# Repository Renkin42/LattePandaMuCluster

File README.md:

Latte Panda Mu Cluster Board
============================

This is a Mini-DTX cluster board for five Latte Panda Mu system-on-modules. Each slot recieves two sata connections, an m.2 M-key slot at pcie gen3x2 and a 2.5gb ethernet 
connection via an RTL8125B. Slot 1 has two USB-3 connections broken out to the rear IO along with HDMI and a single USB Type C port on a front panel header. Slots 2 and 3 
Each have a Front USB-3 connection, a rear USB-3 connection, and an M.2 E-key slot. Slots 4 and 5 have an open-back pcie gen 3x4 slot.

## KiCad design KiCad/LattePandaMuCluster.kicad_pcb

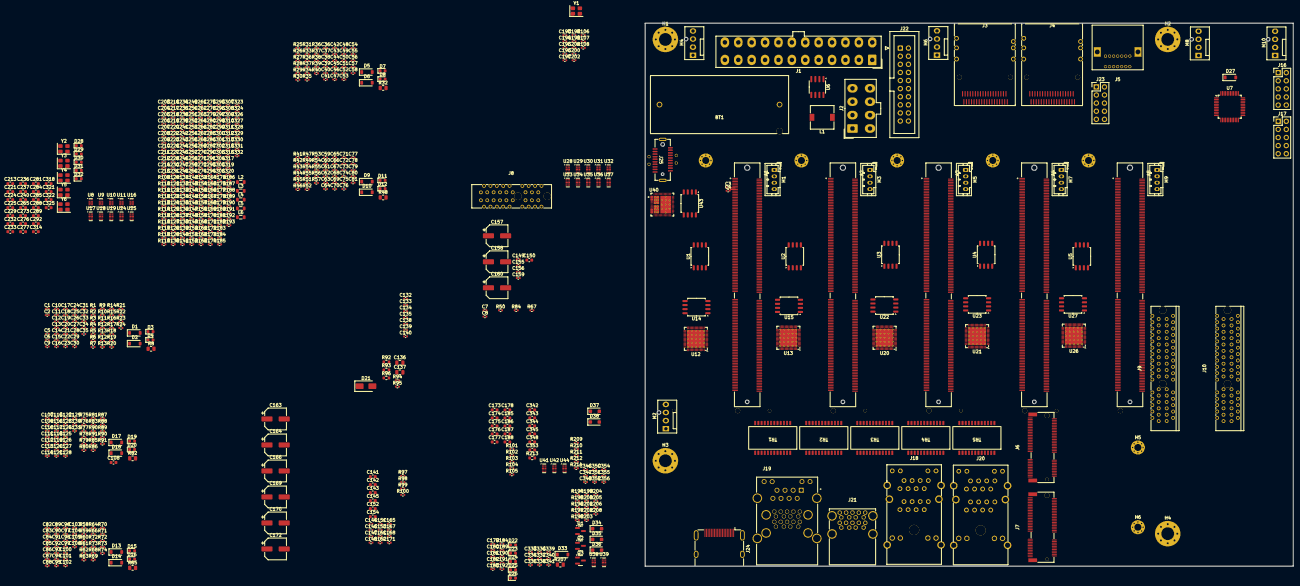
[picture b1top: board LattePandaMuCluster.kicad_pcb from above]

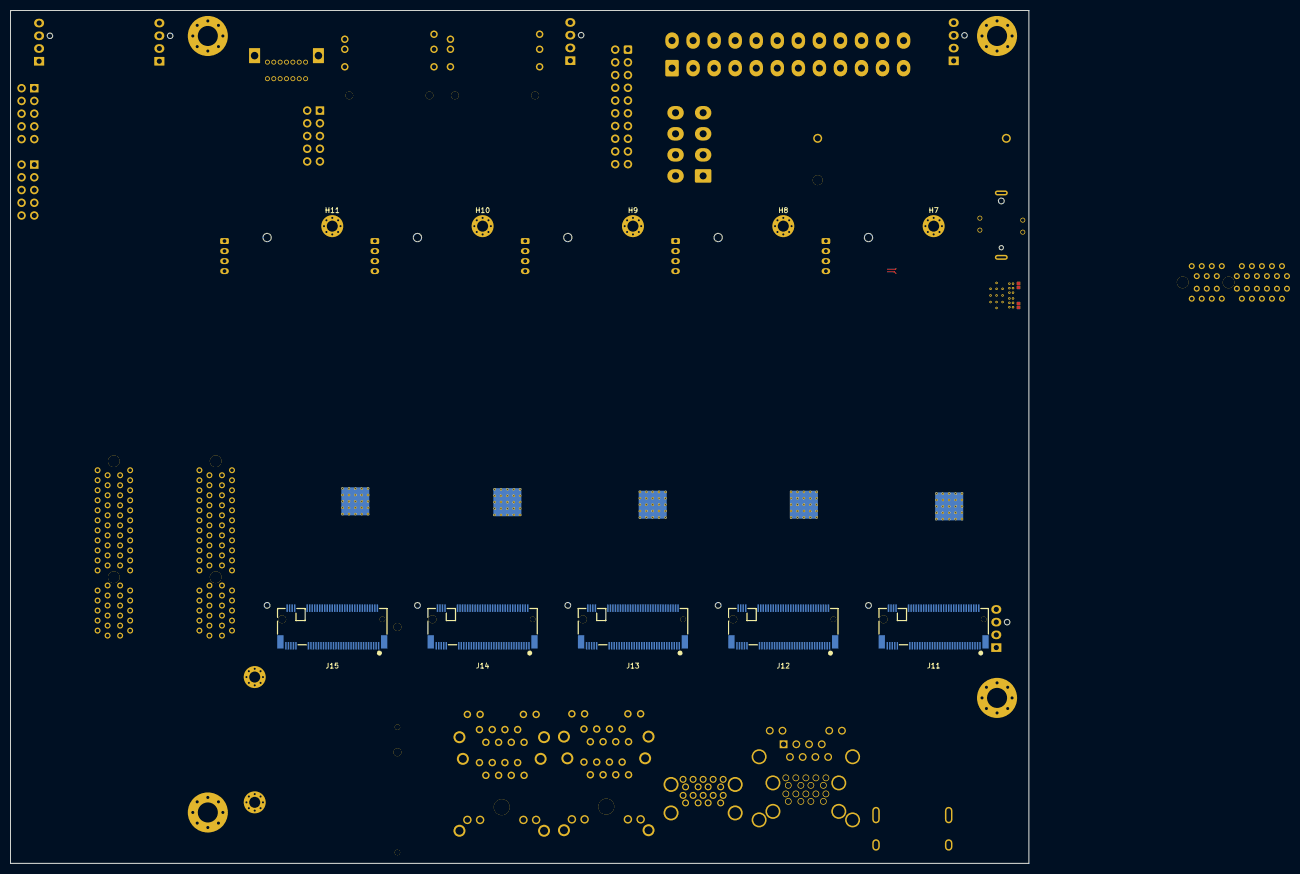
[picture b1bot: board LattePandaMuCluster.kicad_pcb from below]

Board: 4 copper layers, 203.2 x 170.2 mm, 734 parts (10 on the bottom side), 807 nets.

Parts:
A1, A2, A3, A4, A5: LattePanda_Mu; ATTEND_124B-150A02
BT1: Battery_Cell; BAT-TH_BH-123A-A5BJ002
C1, C2, C3, C4, C5, C6, C23, C26, C27, C36, C37, C38, C39, C40, C41, C58, C59, C60, C61, C62, C63, C64, C81, C82, C83, C106, C107, C131, C132, C144, C146, C147, C148, C179, C180, C181, C182, C183, C184, C189, C190, C191, C192, C194, C195, C197, C203, C204, C205, C206, C207, C208, C209, C210, C211, C212, C214, C215, C216, C217, C218, C219, C220, C222, C223, C226, C227, C228, C230, C231, C234, C235, C238, C239, C245, C247, C255, C256, C257, C258, C259, C260, C261, C262, C263, C264, C266, C267, C268, C269, C270, C271, C272, C274, C275, C278, C279, C280, C282, C283, C286, C287, C290, C291, C297, C299, C307, C308, C309, C310, C311, C312, C313, C315, C316, C317, C319, C320, C323, C324, C328, C333, C334, C335, C336, C337, C338, C339, C340, C341, C356: 100nF; C_0402_1005Metric
C7, C8, C9, C10, C11, C12, C21, C22, C30, C31, C34, C35, C42, C43, C44, C45, C46, C47, C56, C57, C65, C66, C67, C68, C69, C70, C79, C80, C84, C85, C86, C87, C88, C89, C90, C91, C92, C93, C94, C95, C104, C105, C109, C110, C111, C112, C113, C114, C115, C116, C117, C118, C119, C120, C129, C130, C241, C242, C243, C244, C293, C294, C295, C296, C326, C327: 220nF; C_0402_1005Metric
C13, C14, C15, C16, C17, C18, C19, C20, C48, C49, C50, C51, C52, C53, C54, C55, C71, C72, C73, C74, C75, C76, C77, C78, C96, C97, C98, C99, C100, C101, C102, C103, C121, C122, C123, C124, C125, C126, C127, C128, C133, C138, C198, C349, C350, C351, C352: 10nF; C_0402_1005Metric
C24, C25, C249, C250, C301, C302, C330: 100pF; C_0402_1005Metric
C28, C29, C32, C33: 330nF; C_0402_1005Metric
C108: 100nF; C_0603_1608Metric
C134, C135, C193: 4.7uF; C_0402_1005Metric
C136, C137: 47uF; C_0805_2012Metric
C139: 1nF; C_0402_1005Metric
C140: 47pF; C_0402_1005Metric
C141, C142, C143, C145, C173, C174, C175, C176, C177, C178, C185, C186, C187, C188, C342, C343, C344, C345, C348: 10uF; C_0603_1608Metric
C149, C151, C153, C155, C156, C159, C161, C162, C165, C167, C168, C171: 100nF/50V; C_0402_1005Metric
C150, C152, C154: 10uF/10V; C_0603_1608Metric
C157, C158, C163, C164, C169, C170: 100uF/25V; CP_Elec_6.3x7.7
C160, C166, C172: 560uF/25V; CP_Elec_6.3x7.7
C196, C199, C200, C346, C347: 1uF; C_0402_1005Metric
C201, C202, C251, C252, C253, C254, C303, C304, C305, C306, C331, C332: 27pF; C_0402_1005Metric
C213, C221, C224, C225, C229, C232, C233, C236, C237, C240, C265, C273, C276, C277, C281, C284, C285, C288, C289, C292, C314, C318, C321, C322, C325, C353: 22uF; C_0603_1608Metric
C246, C248, C298, C300, C329: 390pF; C_0402_1005Metric
C354, C355: 220pF; C_0402_1005Metric
D1, D2, D5, D6, D9, D10, D13, D14, D17, D18, D27, D33: B0520W; D_SOD-123
D3, D4, D7, D8, D11, D12, D15, D16, D19, D20, D22, D23, D24, D25, D26, D28, D29, D30, D31, D32: LED; LED_0603_1608Metric
D21: SSL345F; D_SMA
D34, D35, D36, D37, D38: SMF33A; D_SOD-123F
H1, H2, H3, H4: MountingHole_Pad; MountingHole_4mm_Pad_Via
H5, H6, H7, H8, H9, H10, H11: MountingHole_Pad; MountingHole_2.2mm_M2_Pad_Via
J1: ATX-24; Molex_Mini-Fit_Jr_5566-24A_2x12_P4.20mm_Vertical
J2: Conn_02x04_Top_Bottom; Molex_Mini-Fit_Jr_5566-08A_2x04_P4.20mm_Vertical
J3, J4: SFF-8087; CONN-SMD_LD2136V-MCUL6
J5: SATA; CONN-TH_XUTS-0722-2070
J6, J7: Bus_M.2_Socket_E; CONN-SMD_AS0BC21-S48BE-7H
J8: Bus_PCI_Express_x1; CONN-TH_HYCW05-PCI36-155B
J9, J10: Bus_PCI_Express_x4; PCIE-TH_AAA-PCI-161-K03
J11, J12, J13, J14, J15: Bus_M.2_Socket_M; CONN-SMD_AS0BC21-S30BM-7H
J16, J17, J23: Conn_02x05_Odd_Even; PinHeader_2x05_P2.54mm_Vertical
J18, J20: RJ45_LED_Shielded_x2; RJ45-TH_HC-RJ45-059C
J19: RJE361882415; AMPHENOL_RJE361882415
J21: USB3_A_Stacked; USB-A-TH_HC-USB3.0-L175-2X1-J
J22: USB3_IDC; IDC-Header_2x10_P2.54mm_Vertical
J24: HDMI_A; HDMI_A_Molex_208658-1001_Horizontal
J25: JACK-USBE-20PINTL
L1: 6.8uH; L_7.3x7.3_H3.5
L2, L3, L4, L5, L6: 1uH; L_0805_2012Metric
M1, M3, M5, M7, M9: Fan_4pin; JST_PH_B4B-PH-K_1x04_P2.00mm_Vertical
M2, M4, M6, M8, M10: Fan_4pin; FanPinHeader_1x04_P2.54mm_Vertical
Q1, Q2, Q3: 2N7002; SOT-23
R1, R2, R25, R26, R41, R42, R58, R59, R75, R76: 4.7k; R_0402_1005Metric
R3, R4, R7, R27, R28, R31, R43, R44, R47, R60, R61, R64, R77, R78, R81, R115, R117, R149, R151, R180, R208: 22k; R_0402_1005Metric
R5, R6, R10, R11, R13#2, R14, R15, R16, R17, R18, R29, R30, R45, R46, R62, R63, R79, R80: 100R; R_0402_1005Metric
R8, R32, R48, R65, R82, R207: 1k; R_0805_2012Metric
R9, R12, R33, R34, R49, R51, R66, R68, R83, R85, R101, R102, R103, R104, R105, R202, R203, R205, R206: 2.2k; R_0402_1005Metric
R12#2, R13, R19, R20, R22, R36, R36#2, R37, R37#2, R39, R50, R53, R54, R54#2, R55, R56, R67, R70, R71, R72, R73, R73#2, R84, R87, R88, R90, R90#2, R91, R97, R98, R99, R100, R108, R109, R110, R111, R112, R131, R132, R133, R134, R135, R136, R137, R138, R139, R140, R141, R142, R143, R144, R145, R146, R165, R166, R167, R168, R169, R170, R171, R172, R173, R174, R175, R176, R177, R178, R188, R189, R190, R191, R192, R193, R209, R210, R212, R214: 10k; R_0402_1005Metric
R21, R23, R24, R35, R38, R40, R52, R55#2, R57, R69, R72#2, R74, R86, R89, R91#2, R211: 100k; R_0402_1005Metric
R92: 82k; R_0603_1608Metric
R93: 27k; R_0603_1608Metric
R94: 75k; R_0402_1005Metric
R95: 24k; R_0402_1005Metric
R96: 30k; R_0603_1608Metric
R106, R107, R113, R114, R116, R118, R129, R130, R147, R148, R150, R152, R163, R164, R179, R181, R187: 510R; R_0402_1005Metric
R119, R120, R153, R154, R182: 200R; R_0402_1005Metric
R121, R122, R123, R124, R125, R126, R127, R128, R155, R156, R157, R158, R159, R160, R161, R162, R183, R184, R185, R186: 75R; R_0402_1005Metric
R194, R195, R196, R197, R198, R199, R200, R201: 470R; R_0402_1005Metric
R204: 1M; R_0402_1005Metric
R213: 62k; R_0603_1608Metric
TR1, TR2, TR3, TR4, TR5: QG2439S
U1, U2, U3, U4, U5, U14, U15, U22, U23, U27, U43: ZD25Q64BSIGT; SOIC-8_5.3x5.3mm_P1.27mm
U6: TPS54331; SOIC-8_3.9x4.9mm_P1.27mm
U7: STM32F030C8Tx; LQFP-48_7x7mm_P0.5mm
U8, U9, U10, U11, U16, U17, U18, U19, U24, U25, U28, U29, U30, U31, U32, U33, U34, U35, U36, U37, U38, U39, U41, U42, U44: H5VU25U; Diodes_UDFN-10_1.0x2.5mm_P0.5mm
U12, U13, U20, U21, U26: KTI226V; QFN-56-1EP_7x7mm_P0.4mm_EP5.6x5.6mm_ThermalVias
U40: TPS65987DDJRSHR; RSH0056E-MFG
Y1, Y2, Y3, Y4, Y5, Y6: 25MHz; Crystal_SMD_3225-4Pin_3.2x2.5mm

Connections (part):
+3V3: C23.1, C58.1, C81.1, C106.1, C131.1, C141.1, C142.1, C143.1, C144.1, C145.1, C146.1, C147.1, C148.1, C159.1, C160.1, C165.1, C166.1, C171.1, C172.1, C173.1, C174.1, C175.1, C176.1, C177.1, C178.1, C179.1, C180.1, C181.1, C182.1, C183.1, C184.1, C185.1, C186.1, C187.1, C188.1, C189.1, C190.1, C191.1, C192.1, J1.1 (+3.3V), J1.2 (+3.3V), J1.12 (+3.3V), J1.13 (+3.3V), J6.2 (3.3V), J6.4 (3.3V), J6.72 (3.3V), J6.74 (3.3V), J7.2 (3.3V), J7.4 (3.3V), J7.72 (3.3V), J7.74 (3.3V), J9.A9 (+3.3V), J9.A10 (+3.3V), J9.B8 (+3.3V), J10.A9 (+3.3V), J10.A10 (+3.3V), J10.B8 (+3.3V), J11.2 (3.3V), J11.4 (3.3V), J11.12 (3.3V), J11.14 (3.3V), J11.16 (3.3V), J11.18 (3.3V), J11.70 (3.3V), J11.72 (3.3V), J11.74 (3.3V), J12.2 (3.3V), J12.4 (3.3V), J12.12 (3.3V), J12.14 (3.3V), J12.16 (3.3V), J12.18 (3.3V), J12.70 (3.3V), J12.72 (3.3V), J12.74 (3.3V), J13.2 (3.3V), J13.4 (3.3V), J13.12 (3.3V), J13.14 (3.3V), J13.16 (3.3V)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
+3V3SB: C136.1, C137.1, C149.2, C150.2, C151.2, C152.2, C153.2, C154.2, C203.2, C204.2, C205.1, C206.2, C207.2, C208.1, C211.2, C212.1, C213.2, C214.1, C217.2, C218.1, C221.2, C222.1, C225.2, C226.1, C229.2, C230.1, C233.2, C234.1, C237.2, C238.1, C245.1, C247.1, C255.2, C256.2, C257.1, C258.2, C259.2, C260.1, C263.2, C264.1, C265.2, C266.1, C269.2, C270.1, C273.2, C274.1, C277.2, C278.1, C281.2, C282.1, C285.2, C286.1, C289.2, C290.1, C297.1, C299.1, C307.2, C308.2, C309.1, C310.2, C311.1, C314.2, C315.1, C318.2, C319.1, C322.2, C323.1, C328.1, C348.2, C356.1, D27.2 (A), J9.B10 (3.3Vaux), J10.B10 (3.3Vaux), L1.2, R94.2, R109.1, R110.1, R111.1, R112.1, R113.2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
+5V: C1.1, C36.1, C59.1, C82.1, C107.1, D1.1 (K), D5.1 (K), D9.1 (K), D13.1 (K), D17.1 (K), D33.2 (A), J1.4 (+5V), J1.6 (+5V), J1.21 (+5V), J1.22 (+5V), J1.23 (+5V), M1.2 (+), M3.2 (+), M5.2 (+), M7.2 (+), M9.2 (+), R1.1, R25.1, R41.1, R58.1, R75.1
+5VHDMI: C340.1, D33.1 (K), J24.18 (+5V), R202.1, R203.1
+5VSB: C133.1, C134.1, C135.1, C345.2, C353.1, J1.9 (+5VSB), J16.9, J17.2, J19.U1 (VBUS), J19.U10 (VBUS), J21.1 (VBUS1), J21.10 (VBUS2), J22.1 (VBUS1), J22.11 (VBUS2), J23.1, J23.2, R92.1, U6.2 (VIN), U40.11 (PP_HV1), U40.12 (PP_HV1), U40.25 (PP_CABLE)
+12V: C2.1, C37.1, C60.1, C83.1, C108.1, C155.1, C156.1, C157.1, C158.1, C161.1, C162.1, C163.1, C164.1, C167.1, C168.1, C169.1, C170.1, D2.1 (K), D6.1 (K), D10.1 (K), D14.1 (K), D18.1 (K), J1.10 (+12V), J1.11 (+12V), J9.A2 (+12V), J9.A3 (+12V), J9.B1 (+12V), J9.B2 (+12V), J9.B3 (+12V), J10.A2 (+12V), J10.A3 (+12V), J10.B1 (+12V), J10.B2 (+12V), J10.B3 (+12V), M2.2 (+), M4.2 (+), M6.2 (+), M8.2 (+), M10.2 (+), R2.1, R26.1, R42.1, R59.1, R76.1
+12VCPU: A1.250 (VIN), A1.251 (VIN), A1.252 (VIN), A1.253 (VIN), A1.254 (VIN), A1.255 (VIN), A1.256 (VIN), A1.257 (VIN), A1.258 (VIN), A1.259 (VIN), A1.260 (VIN), A2.250 (VIN), A2.251 (VIN), A2.252 (VIN), A2.253 (VIN), A2.254 (VIN), A2.255 (VIN), A2.256 (VIN), A2.257 (VIN), A2.258 (VIN), A2.259 (VIN), A2.260 (VIN), A3.250 (VIN), A3.251 (VIN), A3.252 (VIN), A3.253 (VIN), A3.254 (VIN), A3.255 (VIN), A3.256 (VIN), A3.257 (VIN), A3.258 (VIN), A3.259 (VIN), A3.260 (VIN), A4.250 (VIN), A4.251 (VIN), A4.252 (VIN), A4.253 (VIN), A4.254 (VIN), A4.255 (VIN), A4.256 (VIN), A4.257 (VIN), A4.258 (VIN), A4.259 (VIN), A4.260 (VIN), A5.250 (VIN), A5.251 (VIN), A5.252 (VIN), A5.253 (VIN), A5.254 (VIN), A5.255 (VIN), A5.256 (VIN), A5.257 (VIN), A5.258 (VIN), A5.259 (VIN), A5.260 (VIN), C344.1, J2.5, J2.6, J2.7, J2.8, U40.1 (PP_HV2), U40.2 (PP_HV2)
+BATT: BT1.1 (+), R8.1, R32.1, R48.1, R65.1, R82.1
/HDMI/SLOT1_HDMI.HPD: A1.183 (DDIB_HPD), Q3.2 (S), R204.2
/HDMI/SLOT1_HDMI.SCL: A1.171 (DDIB_DDC_SCL), Q1.2 (S), R206.2
/HDMI/SLOT1_HDMI.SDA: A1.169 (DDIB_DDC_SDA), Q2.2 (S), R205.2
/HDMI/SLOT1_HDMI.Tx0+: A1.217 (DDIB_TX0+), C333.1
/HDMI/SLOT1_HDMI.Tx0-: A1.215 (DDIB_TX0-), C334.1
/HDMI/SLOT1_HDMI.Tx1+: A1.211 (DDIB_TX1+), C335.1
/HDMI/SLOT1_HDMI.Tx1-: A1.209 (DDIB_TX1-), C336.1
/HDMI/SLOT1_HDMI.Tx2+: A1.205 (DDIB_TX2+), C337.1
/HDMI/SLOT1_HDMI.Tx2-: A1.203 (DDIB_TX2-), C338.1
/HDMI/SLOT1_HDMI.Tx3+: A1.199 (DDIB_TX3+), C339.1
/HDMI/SLOT1_HDMI.Tx3-: A1.197 (DDIB_TX3-), C341.1
/Module 1/ETH.REFCLK+: A1.88 (REFCLK3+), U12.21 (PE_CLK_P)
/Module 1/ETH.REFCLK-: A1.90 (REFCLK3-), U12.22 (PE_CLK_N)
/Module 1/ETH.Rx0+: A1.64 (HSIO6_RX+), C241.1
/Module 1/ETH.Rx0-: A1.66 (HSIO6_RX-), C242.1
/Module 1/ETH.SMBCLK: A1.106 (SMB_CLK), U12.11 (SMB_CLK)
/Module 1/ETH.SMBDAT: A1.108 (SMB_DATA), U12.4 (ULP_WAKE_N), U12.10 (SMB_DATA)
/Module 1/ETH.Tx0+: C21.1, U12.28 (PE_Rx_P)
/Module 1/ETH.Tx0-: C22.1, U12.27 (PE_Rx_N)
/Module 1/HDD_LED: A1.123 (GPP_B14), D4.1 (K), J16.3
/Module 1/M2_EKEY.REFCLK+: A1.94 (REFCLK4+), J7.47 (REFCLKp0)
/Module 1/M2_EKEY.REFCLK-: A1.96 (REFCLK4-), J7.49 (REFCLKn0)
/Module 1/M2_EKEY.Rx0+: A1.28 (HSIO2_RX+), J7.41 (PERp0)
/Module 1/M2_EKEY.Rx0-: A1.30 (HSIO2_RX-), J7.43 (PERn0)
/Module 1/M2_EKEY.Tx0+: C7.1, J7.35 (PETp0)
/Module 1/M2_EKEY.Tx0-: C8.1, J7.37 (PETn0)
/Module 1/NVME.REFCLK+: A1.97 (REFCLK2+), J11.55 (REFCLKp)
/Module 1/NVME.REFCLK-: A1.99 (REFCLK2-), J11.53 (REFCLKn)
/Module 1/NVME.Rx0+: A1.40 (HSIO8_RX+), J11.43 (PERp0/SATA-B-)
/Module 1/NVME.Rx0-: A1.42 (HSIO8_RX-), J11.41 (PERn0/SATA-B+)
/Module 1/NVME.Rx1+: A1.46 (HSIO9_RX+), J11.31 (PERp1)
/Module 1/NVME.Rx1-: A1.48 (HSIO9_RX-), J11.29 (PERn1)
/Module 1/NVME.SUSCLK: A1.131 (SUSCLK), J11.68 (SUSCLK)
/Module 1/NVME.Tx0+: C9.1, J11.49 (PETp0/SATA-A+)
/Module 1/NVME.Tx0-: C10.1, J11.47 (PETn0/SATA-A-)
/Module 1/NVME.Tx1+: C11.1, J11.37 (PETp1)
/Module 1/NVME.Tx1-: C12.1, J11.35 (PETn1)
/Module 1/NVME.~PLTRST: A1.105 (~PLTRST), J7.52 (~PERST0), J11.50 (~PERST), U12.13 (PE_RST_N)
/Module 1/NVME.~WAKE: A1.103 (~WAKE), J7.55 (~PEWAKE0), J11.54 (~PEWAKE), U12.12 (PE_WAKE_N)
/Module 1/PGM_INT: A1.132 (GPP_D2), U40.29 (I2C1_IRQ_N)
/Module 1/PGM_SCL: A1.154 (I2C2_SCL), U40.27 (I2C1_SCL)
/Module 1/PGM_SDA: A1.156 (I2C2_SDA), U40.28 (I2C1_SDA)
/Module 1/RUSB_1.D+: A1.69 (USB2_P1+), J19.U3 (D+), U28.2
/Module 1/RUSB_1.D-: A1.67 (USB2_P1-), J19.U2 (D-), U28.1
/Module 1/RUSB_1.SS_Rx1+: A1.16 (HSIO0_RX+), J19.U6 (SSRX+), U30.4
/Module 1/RUSB_1.SS_Rx1-: A1.18 (HSIO0_RX-), J19.U5 (SSRX-), U30.2
/Module 1/RUSB_1.SS_Tx1+: C3.1, J19.U9 (SSTX+), U30.5
/Module 1/RUSB_1.SS_Tx1-: C4.1, J19.U8 (SSTX-), U30.1
/Module 1/RUSB_2.D+: A1.75 (USB2_P2+), J19.U12 (D+), U28.4
/Module 1/RUSB_2.D-: A1.73 (USB2_P2-), J19.U11 (D-), U28.5
/Module 1/RUSB_2.SS_Rx1+: A1.22 (HSIO1_RX+), J19.U15 (SSRX+), U29.4
/Module 1/RUSB_2.SS_Rx1-: A1.24 (HSIO1_RX-), J19.U14 (SSRX-), U29.2
/Module 1/RUSB_2.SS_Tx1+: C5.1, J19.U18 (SSTX+), U29.5
/Module 1/RUSB_2.SS_Tx1-: C6.1, J19.U17 (SSTX-), U29.1
/Module 1/SATA1.Rx+: C15.1, J3.A2 (Rx0+)
/Module 1/SATA1.Rx-: C16.1, J3.A3 (Rx0-)
/Module 1/SATA1.Tx+: C13.1, J3.B2 (Tx0+)
/Module 1/SATA1.Tx-: C14.1, J3.B3 (Tx0-)
/Module 1/SATA2.Rx+: C19.1, J4.A2 (Rx0+)
/Module 1/SATA2.Rx-: C20.1, J4.A3 (Rx0-)
/Module 1/SATA2.Tx+: C17.1, J4.B2 (Tx0+)
/Module 1/SATA2.Tx-: C18.1, J4.B3 (Tx0-)
/Module 1/SLOT2_UART_RX: A2.139 (UART0_TXD), R11.1
/Module 1/SLOT2_UART_TX: A2.137 (UART0_RXD), R10.1
/Module 1/SLOT3_UART_RX: A3.139 (UART0_TXD), R13#2.2
/Module 1/SLOT3_UART_TX: A3.137 (UART0_RXD), R14.2
/Module 1/SLOT4_UART_RX: A4.139 (UART0_TXD), R15.2
/Module 1/SLOT4_UART_TX: A4.137 (UART0_RXD), R16.2
/Module 1/SLOT5_UART_RX: A5.139 (UART0_TXD), R17.2
/Module 1/SLOT5_UART_TX: A5.137 (UART0_RXD), R18.2
/Module 1/TYPE_C_HEADER.D+: A1.112 (USB2_P6+), J25.18 (D-), U41.4
/Module 1/TYPE_C_HEADER.D-: A1.114 (USB2_P6-), J25.19 (D+), U41.5
/Module 1/TYPE_C_HEADER.SBU1: C24.2, C26.1, C27.1, D37.2 (A2), D38.2 (A2), J25.9 (SBU1), J25.10 (SBU2), R23.1
/Module 1/TYPE_C_HEADER.SS_Rx1+: C32.1, J25.5 (RX1+), U42.5
/Module 1/TYPE_C_HEADER.SS_Rx1-: C33.1, J25.6 (RX1-), U42.4
/Module 1/TYPE_C_HEADER.SS_Rx2+: C28.1, J25.15 (RX2+), U44.1
/Module 1/TYPE_C_HEADER.SS_Rx2-: C29.1, J25.16 (RX2-), U44.2
/Module 1/TYPE_C_HEADER.SS_Tx1+: C34.1, J25.2 (TX1+), U42.1
/Module 1/TYPE_C_HEADER.SS_Tx1-: C35.1, J25.3 (TX1-), U42.2
/Module 1/TYPE_C_HEADER.SS_Tx2+: C30.1, J25.12 (TX2+), U44.5
/Module 1/TYPE_C_HEADER.SS_Tx2-: C31.1, J25.13 (TX2-), U44.4
/Module 1/TYPE_C_HPD: A1.185 (TCP1_HPD), R211.1, U40.30 (HPD(GPIO3))
/Module 1/TYPE_C_SCL: A1.147 (SML1_CLK), U40.32 (I2C2_SCL)
/Module 1/TYPE_C_SDA: A1.145 (SML1_DATA), U40.33 (I2C2_SDA)
/Module 1/~TYPE_C_PMCALERT: A1.125 (GPP_B11), U40.34 (I2C2_IRQ_N)
/Module 2/ETH.REFCLK+: A2.88 (REFCLK3+), U13.21 (PE_CLK_P)
/Module 2/ETH.REFCLK-: A2.90 (REFCLK3-), U13.22 (PE_CLK_N)
/Module 2/ETH.Rx0+: A2.64 (HSIO6_RX+), C243.1
/Module 2/ETH.Rx0-: A2.66 (HSIO6_RX-), C244.1
/Module 2/ETH.SMBCLK: A2.147 (SML1_CLK), U13.11 (SMB_CLK)
/Module 2/ETH.SMBDAT: A2.145 (SML1_DATA), U13.4 (ULP_WAKE_N), U13.10 (SMB_DATA)
/Module 2/ETH.Tx0+: C56.1, U13.28 (PE_Rx_P)
/Module 2/ETH.Tx0-: C57.1, U13.27 (PE_Rx_N)
/Module 2/FUSB.D+: A2.75 (USB2_P2+), J22.3 (D1+), U34.2
/Module 2/FUSB.D-: A2.73 (USB2_P2-), J22.2 (D1-), U34.1
/Module 2/FUSB.SS_Rx1+: A2.22 (HSIO1_RX+), J22.6 (SSRX1+), U36.4
/Module 2/FUSB.SS_Rx1-: A2.24 (HSIO1_RX-), J22.5 (SSRX1-), U36.2
/Module 2/FUSB.SS_Tx1+: C40.1, J22.9 (SSTX1+), U36.5
/Module 2/FUSB.SS_Tx1-: C41.1, J22.8 (SSTX1-), U36.1
/Module 2/M2_EKEY.REFCLK+: A2.94 (REFCLK4+), J6.47 (REFCLKp0)
/Module 2/M2_EKEY.REFCLK-: A2.96 (REFCLK4-), J6.49 (REFCLKn0)
/Module 2/M2_EKEY.Rx0+: A2.28 (HSIO2_RX+), J6.41 (PERp0)
/Module 2/M2_EKEY.Rx0-: A2.30 (HSIO2_RX-), J6.43 (PERn0)
/Module 2/M2_EKEY.Tx0+: C42.1, J6.35 (PETp0)
/Module 2/M2_EKEY.Tx0-: C43.1, J6.37 (PETn0)
/Module 2/M2_EKEY.USB-D+: A2.81 (USB2_P3+), J6.3 (USB_D+)
/Module 2/M2_EKEY.USB-D-: A2.79 (USB2_P3-), J6.5 (USB_D-)
/Module 2/NVME.REFCLK+: A2.97 (REFCLK2+), J12.55 (REFCLKp)
/Module 2/NVME.REFCLK-: A2.99 (REFCLK2-), J12.53 (REFCLKn)
/Module 2/NVME.Rx0+: A2.40 (HSIO8_RX+), J12.43 (PERp0/SATA-B-)
/Module 2/NVME.Rx0-: A2.42 (HSIO8_RX-), J12.41 (PERn0/SATA-B+)
/Module 2/NVME.Rx1+: A2.46 (HSIO9_RX+), J12.31 (PERp1)
/Module 2/NVME.Rx1-: A2.48 (HSIO9_RX-), J12.29 (PERn1)
/Module 2/NVME.SUSCLK: A2.131 (SUSCLK), J6.50 (SUSCLK), J12.68 (SUSCLK)
/Module 2/NVME.Tx0+: C44.1, J12.49 (PETp0/SATA-A+)
/Module 2/NVME.Tx0-: C45.1, J12.47 (PETn0/SATA-A-)
/Module 2/NVME.Tx1+: C46.1, J12.37 (PETp1)
/Module 2/NVME.Tx1-: C47.1, J12.35 (PETn1)
/Module 2/NVME.~PLTRST: A2.105 (~PLTRST), J6.52 (~PERST0), J12.50 (~PERST), U13.13 (PE_RST_N)
/Module 2/NVME.~WAKE: A2.103 (~WAKE), J6.55 (~PEWAKE0), J12.54 (~PEWAKE), U13.12 (PE_WAKE_N)
/Module 2/RUSB.D+: A2.69 (USB2_P1+), J21.3 (D1+), U31.2
/Module 2/RUSB.D-: A2.67 (USB2_P1-), J21.2 (D1-), U31.1
/Module 2/RUSB.SS_Rx1+: A2.16 (HSIO0_RX+), J21.6 (SSRX1+), U33.4
/Module 2/RUSB.SS_Rx1-: A2.18 (HSIO0_RX-), J21.5 (SSRX1-), U33.2
/Module 2/RUSB.SS_Tx1+: C38.1, J21.9 (SSTX1+), U33.5
/Module 2/RUSB.SS_Tx1-: C39.1, J21.8 (SSTX1-), U33.1
/Module 2/SATA1.Rx+: C50.1, J3.A5 (Rx1+)
/Module 2/SATA1.Rx-: C51.1, J3.A6 (Rx1-)
/Module 2/SATA1.Tx+: C48.1, J3.B5 (Tx1+)
/Module 2/SATA1.Tx-: C49.1, J3.B6 (Tx1-)
/Module 2/SATA2.Rx+: C54.1, J4.A5 (Rx1+)
/Module 2/SATA2.Rx-: C55.1, J4.A6 (Rx1-)
/Module 2/SATA2.Tx+: C52.1, J4.B5 (Tx1+)
/Module 2/SATA2.Tx-: C53.1, J4.B6 (Tx1-)
/Module 3/ETH.REFCLK+: A3.88 (REFCLK3+), U20.21 (PE_CLK_P)
/Module 3/ETH.REFCLK-: A3.90 (REFCLK3-), U20.22 (PE_CLK_N)
/Module 3/ETH.Rx0+: A3.64 (HSIO6_RX+), C293.1
/Module 3/ETH.Rx0-: A3.66 (HSIO6_RX-), C294.1
/Module 3/ETH.SMBCLK: A3.106 (SMB_CLK), U20.11 (SMB_CLK)
/Module 3/ETH.SMBDAT: A3.108 (SMB_DATA), U20.4 (ULP_WAKE_N), U20.10 (SMB_DATA)
/Module 3/ETH.Tx0+: C79.1, U20.28 (PE_Rx_P)
/Module 3/ETH.Tx0-: C80.1, U20.27 (PE_Rx_N)
/Module 3/FUSB.D+: A3.75 (USB2_P2+), J22.13 (D2+), U34.4
/Module 3/FUSB.D-: A3.73 (USB2_P2-), J22.12 (D2-), U34.5
/Module 3/FUSB.SS_Rx1+: A3.22 (HSIO1_RX+), J22.16 (SSRX2+), U35.4
/Module 3/FUSB.SS_Rx1-: A3.24 (HSIO1_RX-), J22.15 (SSRX2-), U35.2
/Module 3/FUSB.SS_Tx1+: C63.1, J22.19 (SSTX2+), U35.5
/Module 3/FUSB.SS_Tx1-: C64.1, J22.18 (SSTX2-), U35.1
/Module 3/NVME.REFCLK+: A3.97 (REFCLK2+), J13.55 (REFCLKp)
/Module 3/NVME.REFCLK-: A3.99 (REFCLK2-), J13.53 (REFCLKn)
/Module 3/NVME.Rx0+: A3.40 (HSIO8_RX+), J13.43 (PERp0/SATA-B-)
/Module 3/NVME.Rx0-: A3.42 (HSIO8_RX-), J13.41 (PERn0/SATA-B+)
/Module 3/NVME.Rx1+: A3.46 (HSIO9_RX+), J13.31 (PERp1)
/Module 3/NVME.Rx1-: A3.48 (HSIO9_RX-), J13.29 (PERn1)
/Module 3/NVME.SUSCLK: A3.131 (SUSCLK), J13.68 (SUSCLK)
/Module 3/NVME.Tx0+: C67.1, J13.49 (PETp0/SATA-A+)
/Module 3/NVME.Tx0-: C68.1, J13.47 (PETn0/SATA-A-)
/Module 3/NVME.Tx1+: C69.1, J13.37 (PETp1)
/Module 3/NVME.Tx1-: C70.1, J13.35 (PETn1)
/Module 3/NVME.~PLTRST: A3.105 (~PLTRST), J13.50 (~PERST), U20.13 (PE_RST_N)
/Module 3/NVME.~WAKE: A3.103 (~WAKE), J13.54 (~PEWAKE), U20.12 (PE_WAKE_N)
/Module 3/RUSB.D+: A3.69 (USB2_P1+), J21.12 (D2+), U31.4
/Module 3/RUSB.D-: A3.67 (USB2_P1-), J21.11 (D2-), U31.5
/Module 3/RUSB.SS_Rx1+: A3.16 (HSIO0_RX+), J21.15 (SSRX2+), U32.4
/Module 3/RUSB.SS_Rx1-: A3.18 (HSIO0_RX-), J21.14 (SSRX2-), U32.2
/Module 3/RUSB.SS_Tx1+: C61.1, J21.18 (SSTX2+), U32.5
/Module 3/RUSB.SS_Tx1-: C62.1, J21.17 (SSTX2-), U32.1
/Module 3/SATA1.Rx+: C73.1, J3.A13 (Rx2+)
/Module 3/SATA1.Rx-: C74.1, J3.A14 (Rx2-)
/Module 3/SATA1.Tx+: C71.1, J3.B13 (Tx2+)
/Module 3/SATA1.Tx-: C72.1, J3.B14 (Tx2-)
/Module 3/SATA2.Rx+: C77.1, J4.A13 (Rx2+)
/Module 3/SATA2.Rx-: C78.1, J4.A14 (Rx2-)
/Module 3/SATA2.Tx+: C75.1, J4.B13 (Tx2+)
/Module 3/SATA2.Tx-: C76.1, J4.B14 (Tx2-)
/Module 4/ETH.REFCLK+: A4.88 (REFCLK3+), U21.21 (PE_CLK_P)
/Module 4/ETH.REFCLK-: A4.90 (REFCLK3-), U21.22 (PE_CLK_N)
/Module 4/ETH.Rx0+: A4.64 (HSIO6_RX+), C295.1
/Module 4/ETH.Rx0-: A4.66 (HSIO6_RX-), C296.1
/Module 4/ETH.Tx0+: C104.1, U21.28 (PE_Rx_P)
/Module 4/ETH.Tx0-: C105.1, U21.27 (PE_Rx_N)
/Module 4/FUSB_D+: A4.69 (USB2_P1+), J23.5, U37.5
/Module 4/FUSB_D-: A4.67 (USB2_P1-), J23.3, U37.4
/Module 4/NVME.REFCLK+: A4.97 (REFCLK2+), J15.55 (REFCLKp)
/Module 4/NVME.REFCLK-: A4.99 (REFCLK2-), J15.53 (REFCLKn)
/Module 4/NVME.Rx0+: A4.40 (HSIO8_RX+), J15.43 (PERp0/SATA-B-)
/Module 4/NVME.Rx0-: A4.42 (HSIO8_RX-), J15.41 (PERn0/SATA-B+)
/Module 4/NVME.SUSCLK: A4.131 (SUSCLK), J15.68 (SUSCLK)
/Module 4/NVME.Tx0+: C92.1, J15.49 (PETp0/SATA-A+)
/Module 4/NVME.Tx0-: C93.1, J15.47 (PETn0/SATA-A-)
/Module 4/NVME.~PLTRST: A4.105 (~PLTRST), J9.A11 (~PERST), J15.50 (~PERST), U21.13 (PE_RST_N)
/Module 4/NVME.~WAKE: A4.103 (~WAKE), J9.B11 (~WAKE), J15.54 (~PEWAKE), U21.12 (PE_WAKE_N)
/Module 4/PCIE_X4.REFCLK+: A4.94 (REFCLK4+), J9.A13 (REFCLK+)
/Module 4/PCIE_X4.REFCLK-: A4.96 (REFCLK4-), J9.A14 (REFCLK-)
/Module 4/PCIE_X4.Rx0+: A4.16 (HSIO0_RX+), J9.A16 (PERp0)
/Module 4/PCIE_X4.Rx0-: A4.18 (HSIO0_RX-), J9.A17 (PERn0)
/Module 4/PCIE_X4.Rx2+: A4.28 (HSIO2_RX+), J9.A25 (PERp2)
/Module 4/PCIE_X4.Rx2-: A4.30 (HSIO2_RX-), J9.A26 (PERn2)
/Module 4/PCIE_X4.Rx3+: A4.34 (HSIO3_RX+), J9.A29 (PERp3)
/Module 4/PCIE_X4.Rx3-: A4.36 (HSIO3_RX-), J9.A30 (PERn3)
/Module 4/PCIE_X4.SMBCLK: A4.106 (SMB_CLK), J9.B5 (SMCLK), U21.11 (SMB_CLK)
/Module 4/PCIE_X4.SMBDAT: A4.108 (SMB_DATA), J9.B6 (SMDAT), U21.4 (ULP_WAKE_N), U21.10 (SMB_DATA)
/Module 4/PCIE_X4.Tx0+: C84.1, J9.B14 (PETp0)
/Module 4/PCIE_X4.Tx0-: C85.1, J9.B15 (PETn0)
/Module 4/PCIE_X4.Tx2+: C88.1, J9.B23 (PETp2)
/Module 4/PCIE_X4.Tx2-: C89.1, J9.B24 (PETn2)
/Module 4/PCIE_X4.Tx3+: C90.1, J9.B27 (PETp3)
/Module 4/PCIE_X4.Tx3-: C91.1, J9.B28 (PETn3)
/Module 4/SATA1.Rx+: C98.1, J3.A16 (Rx3+)
/Module 4/SATA1.Rx-: C99.1, J3.A17 (Rx3-)
/Module 4/SATA1.Tx+: C96.1, J3.B16 (Tx3+)
/Module 4/SATA1.Tx-: C97.1, J3.B17 (Tx3-)
/Module 4/SATA2.Rx+: C102.1, J4.A16 (Rx3+)
/Module 4/SATA2.Rx-: C103.1, J4.A17 (Rx3-)
/Module 4/SATA2.Tx+: C100.1, J4.B16 (Tx3+)
/Module 4/SATA2.Tx-: C101.1, J4.B17 (Tx3-)
/Module 5/ETH.REFCLK+: A5.88 (REFCLK3+), U26.21 (PE_CLK_P)
/Module 5/ETH.REFCLK-: A5.90 (REFCLK3-), U26.22 (PE_CLK_N)
/Module 5/ETH.Rx0+: A5.64 (HSIO6_RX+), C326.1
/Module 5/ETH.Rx0-: A5.66 (HSIO6_RX-), C327.1
/Module 5/ETH.Tx0+: C129.1, U26.28 (PE_Rx_P)
/Module 5/ETH.Tx0-: C130.1, U26.27 (PE_Rx_N)
/Module 5/FUSB_D+: A5.69 (USB2_P1+), J23.6, U37.2
/Module 5/FUSB_D-: A5.67 (USB2_P1-), J23.4, U37.1
/Module 5/NVME.REFCLK+: A5.97 (REFCLK2+), J14.55 (REFCLKp)
/Module 5/NVME.REFCLK-: A5.99 (REFCLK2-), J14.53 (REFCLKn)
/Module 5/NVME.Rx0+: A5.40 (HSIO8_RX+), J14.43 (PERp0/SATA-B-)
/Module 5/NVME.Rx0-: A5.42 (HSIO8_RX-), J14.41 (PERn0/SATA-B+)
/Module 5/NVME.Rx1+: A5.46 (HSIO9_RX+), J14.31 (PERp1)
/Module 5/NVME.Rx1-: A5.48 (HSIO9_RX-), J14.29 (PERn1)
/Module 5/NVME.SUSCLK: A5.131 (SUSCLK), J14.68 (SUSCLK)
/Module 5/NVME.Tx0+: C117.1, J14.49 (PETp0/SATA-A+)
/Module 5/NVME.Tx0-: C118.1, J14.47 (PETn0/SATA-A-)
/Module 5/NVME.Tx1+: C119.1, J14.37 (PETp1)
/Module 5/NVME.Tx1-: C120.1, J14.35 (PETn1)
/Module 5/NVME.~PLTRST: A5.105 (~PLTRST), J10.A11 (~PERST), J14.50 (~PERST), U26.13 (PE_RST_N)
/Module 5/NVME.~WAKE: A5.103 (~WAKE), J10.B11 (~WAKE), J14.54 (~PEWAKE), U26.12 (PE_WAKE_N)
/Module 5/PCIE_X4.REFCLK+: A5.94 (REFCLK4+), J10.A13 (REFCLK+)
/Module 5/PCIE_X4.REFCLK-: A5.96 (REFCLK4-), J10.A14 (REFCLK-)
/Module 5/PCIE_X4.Rx0+: A5.16 (HSIO0_RX+), J10.A16 (PERp0)
/Module 5/PCIE_X4.Rx0-: A5.18 (HSIO0_RX-), J10.A17 (PERn0)
/Module 5/PCIE_X4.Rx1+: A5.22 (HSIO1_RX+), J10.A21 (PERp1)
/Module 5/PCIE_X4.Rx1-: A5.24 (HSIO1_RX-), J10.A22 (PERn1)
/Module 5/PCIE_X4.Rx2+: A5.28 (HSIO2_RX+), J10.A25 (PERp2)
/Module 5/PCIE_X4.Rx2-: A5.30 (HSIO2_RX-), J10.A26 (PERn2)
/Module 5/PCIE_X4.Rx3+: A5.34 (HSIO3_RX+), J10.A29 (PERp3)
/Module 5/PCIE_X4.Rx3-: A5.36 (HSIO3_RX-), J10.A30 (PERn3)
/Module 5/PCIE_X4.SMBCLK: A5.106 (SMB_CLK), J10.B5 (SMCLK), U26.11 (SMB_CLK)
/Module 5/PCIE_X4.SMBDAT: A5.108 (SMB_DATA), J10.B6 (SMDAT), U26.4 (ULP_WAKE_N), U26.10 (SMB_DATA)
/Module 5/PCIE_X4.Tx0+: C109.1, J10.B14 (PETp0)
/Module 5/PCIE_X4.Tx0-: C110.1, J10.B15 (PETn0)
/Module 5/PCIE_X4.Tx1+: C111.1, J10.B19 (PETp1)
/Module 5/PCIE_X4.Tx1-: C112.1, J10.B20 (PETn1)
/Module 5/PCIE_X4.Tx2+: C113.1, J10.B23 (PETp2)
/Module 5/PCIE_X4.Tx2-: C114.1, J10.B24 (PETn2)
/Module 5/PCIE_X4.Tx3+: C115.1, J10.B27 (PETp3)
/Module 5/PCIE_X4.Tx3-: C116.1, J10.B28 (PETn3)
/Module 5/SATA1.Rx+: C123.1, J5.6 (Rx+)
/Module 5/SATA1.Rx-: C124.1, J5.5 (Rx-)
/Module 5/SATA1.Tx+: C121.1, J5.2 (Tx+)
/Module 5/SATA1.Tx-: C122.1, J5.3 (Tx-)
/Module 5/SATA2.Rx+: C127.1, J5.S6 (Rx+)
/Module 5/SATA2.Rx-: C128.1, J5.S5 (Rx-)
/Module 5/SATA2.Tx+: C125.1, J5.S2 (Tx+)
/Module 5/SATA2.Tx-: C126.1, J5.S3 (Tx-)
/PSU/PS_ON: J1.16 (PS_ON#), U7.13 (PA3)
/PSU/PWR_OK: J1.8 (PWR_OK), J16.4, U7.14 (PA4)
/STM32/PWRBTN1: A1.1 (~PWRBTN), U7.41 (PB5)
/STM32/PWRBTN2: A2.1 (~PWRBTN), U7.42 (PB6)
/STM32/PWRBTN3: A3.1 (~PWRBTN), U7.43 (PB7)
/STM32/PWRBTN4: A4.1 (~PWRBTN), U7.45 (PB8)
/STM32/PWRBTN5: A5.1 (~PWRBTN), U7.46 (PB9)
/STM32/PWRON1: A1.7 (SLS_S3), U7.18 (PB0)
/STM32/PWRON2: A2.7 (SLS_S3), U7.19 (PB1)
/STM32/PWRON3: A3.7 (SLS_S3), U7.20 (PB2)
/STM32/PWRON4: A4.7 (SLS_S3), U7.39 (PB3)
/STM32/PWRON5: A5.7 (SLS_S3), U7.40 (PB4)
/STM32/RSTBTN1: A1.3 (~RSTBTN), U7.21 (PB10)
/STM32/RSTBTN2: A2.3 (~RSTBTN), U7.22 (PB11)
/STM32/RSTBTN3: A3.3 (~RSTBTN), U7.25 (PB12)
/STM32/RSTBTN4: A4.3 (~RSTBTN), U7.26 (PB13)
/STM32/RSTBTN5: A5.3 (~RSTBTN), U7.27 (PB14)
/USB Type C/LDO_3V3: C342.2, R213.1, U40.9 (LDO_3V3)
GND: A1.11 (GND), A1.14 (GND), A1.17 (GND), A1.20 (GND), A1.23 (GND), A1.26 (GND), A1.29 (GND), A1.32 (GND), A1.35 (GND), A1.38 (GND), A1.41 (GND), A1.44 (GND), A1.47 (GND), A1.50 (GND), A1.53 (GND), A1.56 (GND), A1.59 (GND), A1.62 (GND), A1.65 (GND), A1.68 (GND), A1.71 (GND), A1.74 (GND), A1.77 (GND), A1.80 (GND), A1.83 (GND), A1.86 (GND), A1.89 (GND), A1.92 (GND), A1.95 (GND), A1.98 (GND), A1.101 (GND), A1.107 (GND), A1.110 (GND), A1.113 (GND), A1.116 (GND), A1.135 (GND), A1.136 (GND), A1.151 (GND), A1.158 (GND), A1.167 (GND), A1.170 (GND), A1.181 (GND), A1.182 (GND), A1.188 (GND), A1.189 (GND), A1.194 (GND), A1.195 (GND), A1.200 (GND), A1.201 (GND), A1.206 (GND), A1.207 (GND), A1.212 (GND), A1.213 (GND), A1.218 (GND), A1.219 (GND), A1.224 (GND), A1.225 (GND), A1.230 (GND), A1.231 (GND), A1.236 (GND), A1.237 (GND), A1.242 (GND), A1.243 (GND), A1.248 (GND), A1.249 (GND), A2.11 (GND), A2.14 (GND), A2.17 (GND), A2.20 (GND), A2.23 (GND), A2.26 (GND), A2.29 (GND), A2.32 (GND), A2.35 (GND), A2.38 (GND), A2.41 (GND), A2.44 (GND), A2.47 (GND), A2.50 (GND), A2.53 (GND)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
unnamed: A1.2 (FAN1_PWM), R5.1
unnamed: A1.4 (FAN1_TAC), R3.1
unnamed: A1.6 (FAN2_PWM), R6.1
unnamed: A1.8 (FAN2_TAC), R4.1, R7.1
unnamed: A1.13 (HSIO0_TX+), C3.2
unnamed: A1.15 (HSIO0_TX-), C4.2
unnamed: A1.19 (HSIO1_TX+), C5.2
unnamed: A1.21 (HSIO1_TX-), C6.2
unnamed: A1.25 (HSIO2_TX+), C7.2
unnamed: A1.27 (HSIO2_TX-), C8.2
unnamed: A1.61 (HSIO6_TX+), C21.2
unnamed: A1.63 (HSIO6_TX-), C22.2
unnamed: A1.37 (HSIO8_TX+), C9.2
unnamed: A1.39 (HSIO8_TX-), C10.2
unnamed: A1.43 (HSIO9_TX+), C11.2
unnamed: A1.45 (HSIO9_TX-), C12.2
unnamed: A1.52 (HSIO10_RX+), C15.2
unnamed: A1.54 (HSIO10_RX-), C16.2
unnamed: A1.49 (HSIO10_TX+), C13.2
unnamed: A1.51 (HSIO10_TX-), C14.2
unnamed: A1.58 (HSIO11_RX+), C19.2
unnamed: A1.60 (HSIO11_RX-), C20.2
unnamed: A1.55 (HSIO11_TX+), C17.2
unnamed: A1.57 (HSIO11_TX-), C18.2
unnamed: A1.12 (SIO_UART_RX), R11.2
unnamed: A1.10 (SIO_UART_TX), R10.2
unnamed: A1.5 (SLS_S0), D3.1 (K)
unnamed: A1.155 (SPI_CLK), U1.6 (CLK)
unnamed: A1.161 (SPI_IO2), R20.2, U1.3 (~WP/IO_{2})
unnamed: A1.153 (SPI_IO3), R19.2, U1.7 (~HOLD/~RESET/IO_{3})
unnamed: A1.163 (SPI_MISO/SPI_IO1), U1.2 (DO/IO_{1})
unnamed: A1.159 (SPI_MOSI/SPI_IO0), U1.5 (DI/IO_{0})
unnamed: A1.187 (TCP0_HPD), R21.2
unnamed: A1.244 (TCP1_AUX+), C26.2
unnamed: A1.246 (TCP1_AUX-), C27.2
unnamed: A1.175 (TCP1_DDC_SCL), R24.2
unnamed: A1.173 (TCP1_DDC_SDA), R23.2
unnamed: A1.220 (TCP1_TX0+), C34.2
unnamed: A1.222 (TCP1_TX0-), C35.2
unnamed: A1.232 (TCP1_TX1+), C30.2
unnamed: A1.234 (TCP1_TX1-), C31.2
unnamed: A1.226 (TCP1_TXRX0+), C32.2
unnamed: A1.228 (TCP1_TXRX0-), C33.2
unnamed: A1.238 (TCP1_TXRX1+), C28.2
unnamed: A1.240 (TCP1_TXRX1-), C29.2
unnamed: A1.137 (UART0_RXD), R13#2.1
unnamed: A1.139 (UART0_TXD), R14.1
unnamed: A1.141 (UART1_RXD), R15.1
unnamed: A1.143 (UART1_TXD), R16.1
unnamed: A1.140 (UART2_RXD), R17.1
unnamed: A1.138 (UART2_TXD), R18.1
unnamed: A1.115 (VBAT), R8.2
unnamed: A1.133 (~BIOS_SEL), R22.1
unnamed: A1.165 (~SPI_CS), U1.1 (~CS)
unnamed: A2.183 (DDIB_HPD), R35.2
unnamed: A2.2 (FAN1_PWM), R29.1
unnamed: A2.4 (FAN1_TAC), R27.1
unnamed: A2.6 (FAN2_PWM), R30.1
unnamed: A2.8 (FAN2_TAC), R28.1, R31.1
unnamed: A2.121 (GPP_A12), D8.1 (K)
unnamed: A2.13 (HSIO0_TX+), C38.2
unnamed: A2.15 (HSIO0_TX-), C39.2
unnamed: A2.19 (HSIO1_TX+), C40.2
unnamed: A2.21 (HSIO1_TX-), C41.2
unnamed: A2.25 (HSIO2_TX+), C42.2
unnamed: A2.27 (HSIO2_TX-), C43.2
unnamed: A2.61 (HSIO6_TX+), C56.2
unnamed: A2.63 (HSIO6_TX-), C57.2
unnamed: A2.37 (HSIO8_TX+), C44.2
unnamed: A2.39 (HSIO8_TX-), C45.2
unnamed: A2.43 (HSIO9_TX+), C46.2
unnamed: A2.45 (HSIO9_TX-), C47.2
unnamed: A2.52 (HSIO10_RX+), C50.2
unnamed: A2.54 (HSIO10_RX-), C51.2
unnamed: A2.49 (HSIO10_TX+), C48.2
unnamed: A2.51 (HSIO10_TX-), C49.2
unnamed: A2.58 (HSIO11_RX+), C54.2
unnamed: A2.60 (HSIO11_RX-), C55.2
unnamed: A2.55 (HSIO11_TX+), C52.2
unnamed: A2.57 (HSIO11_TX-), C53.2
unnamed: A2.5 (SLS_S0), D7.1 (K)
unnamed: A2.155 (SPI_CLK), U2.6 (CLK)
unnamed: A2.161 (SPI_IO2), R37.2, U2.3 (~WP/IO_{2})
unnamed: A2.153 (SPI_IO3), R36.2, U2.7 (~HOLD/~RESET/IO_{3})
unnamed: A2.163 (SPI_MISO/SPI_IO1), U2.2 (DO/IO_{1})
unnamed: A2.159 (SPI_MOSI/SPI_IO0), U2.5 (DI/IO_{0})
unnamed: A2.187 (TCP0_HPD), R38.2
unnamed: A2.185 (TCP1_HPD), R40.2
unnamed: A2.115 (VBAT), R32.2
unnamed: A2.133 (~BIOS_SEL), R39.1
unnamed: A2.165 (~SPI_CS), U2.1 (~CS)
unnamed: A3.183 (DDIB_HPD), R52.2
unnamed: A3.2 (FAN1_PWM), R45.1
unnamed: A3.4 (FAN1_TAC), R43.1
unnamed: A3.6 (FAN2_PWM), R46.1
unnamed: A3.8 (FAN2_TAC), R44.1, R47.1
unnamed: A3.123 (GPP_B14), D12.1 (K)
unnamed: A3.13 (HSIO0_TX+), C61.2
unnamed: A3.15 (HSIO0_TX-), C62.2
unnamed: A3.19 (HSIO1_TX+), C63.2
unnamed: A3.21 (HSIO1_TX-), C64.2
unnamed: A3.25 (HSIO2_TX+), C65.2
unnamed: A3.27 (HSIO2_TX-), C66.2
unnamed: A3.61 (HSIO6_TX+), C79.2
unnamed: A3.63 (HSIO6_TX-), C80.2
unnamed: A3.37 (HSIO8_TX+), C67.2
unnamed: A3.39 (HSIO8_TX-), C68.2
unnamed: A3.43 (HSIO9_TX+), C69.2
unnamed: A3.45 (HSIO9_TX-), C70.2
unnamed: A3.52 (HSIO10_RX+), C73.2
unnamed: A3.54 (HSIO10_RX-), C74.2
unnamed: A3.49 (HSIO10_TX+), C71.2
unnamed: A3.51 (HSIO10_TX-), C72.2
unnamed: A3.58 (HSIO11_RX+), C77.2
unnamed: A3.60 (HSIO11_RX-), C78.2
unnamed: A3.55 (HSIO11_TX+), C75.2
unnamed: A3.57 (HSIO11_TX-), C76.2
unnamed: A3.5 (SLS_S0), D11.1 (K)
unnamed: A3.155 (SPI_CLK), U3.6 (CLK)
unnamed: A3.161 (SPI_IO2), R54.2, U3.3 (~WP/IO_{2})
unnamed: A3.153 (SPI_IO3), R53.2, U3.7 (~HOLD/~RESET/IO_{3})
unnamed: A3.163 (SPI_MISO/SPI_IO1), U3.2 (DO/IO_{1})
unnamed: A3.159 (SPI_MOSI/SPI_IO0), U3.5 (DI/IO_{0})
unnamed: A3.187 (TCP0_HPD), R55#2.2
unnamed: A3.185 (TCP1_HPD), R57.2
unnamed: A3.115 (VBAT), R48.2
unnamed: A3.133 (~BIOS_SEL), R56.1
unnamed: A3.102 (~CLKREQ4), R50.1, R55.1
unnamed: A3.165 (~SPI_CS), U3.1 (~CS)
unnamed: A4.183 (DDIB_HPD), R69.2
unnamed: A4.2 (FAN1_PWM), R62.1
unnamed: A4.4 (FAN1_TAC), R60.1
unnamed: A4.6 (FAN2_PWM), R63.1
unnamed: A4.8 (FAN2_TAC), R61.1, R64.1
unnamed: A4.13 (HSIO0_TX+), C84.2
unnamed: A4.15 (HSIO0_TX-), C85.2
unnamed: A4.19 (HSIO1_TX+), C86.2
unnamed: A4.21 (HSIO1_TX-), C87.2
unnamed: A4.25 (HSIO2_TX+), C88.2
unnamed: A4.27 (HSIO2_TX-), C89.2
unnamed: A4.31 (HSIO3_TX+), C90.2
unnamed: A4.33 (HSIO3_TX-), C91.2
unnamed: A4.61 (HSIO6_TX+), C104.2
unnamed: A4.63 (HSIO6_TX-), C105.2
unnamed: A4.37 (HSIO8_TX+), C92.2
unnamed: A4.39 (HSIO8_TX-), C93.2
unnamed: A4.43 (HSIO9_TX+), C94.2
unnamed: A4.45 (HSIO9_TX-), C95.2
unnamed: A4.52 (HSIO10_RX+), C98.2
unnamed: A4.54 (HSIO10_RX-), C99.2
unnamed: A4.49 (HSIO10_TX+), C96.2
unnamed: A4.51 (HSIO10_TX-), C97.2
unnamed: A4.58 (HSIO11_RX+), C102.2
unnamed: A4.60 (HSIO11_RX-), C103.2
unnamed: A4.55 (HSIO11_TX+), C100.2
unnamed: A4.57 (HSIO11_TX-), C101.2
unnamed: A4.5 (SLS_S0), D15.1 (K)
unnamed: A4.155 (SPI_CLK), U4.6 (CLK)
unnamed: A4.161 (SPI_IO2), R71.2, U4.3 (~WP/IO_{2})
unnamed: A4.153 (SPI_IO3), R70.2, U4.7 (~HOLD/~RESET/IO_{3})
unnamed: A4.163 (SPI_MISO/SPI_IO1), U4.2 (DO/IO_{1})
unnamed: A4.159 (SPI_MOSI/SPI_IO0), U4.5 (DI/IO_{0})
unnamed: A4.187 (TCP0_HPD), R72#2.2
unnamed: A4.185 (TCP1_HPD), R74.2
unnamed: A4.115 (VBAT), R65.2
unnamed: A4.133 (~BIOS_SEL), R73#2.1
unnamed: A4.102 (~CLKREQ4), R67.1, R73.1
unnamed: A4.165 (~SPI_CS), U4.1 (~CS)
unnamed: A5.183 (DDIB_HPD), R86.2
unnamed: A5.2 (FAN1_PWM), R79.1
unnamed: A5.4 (FAN1_TAC), R77.1
unnamed: A5.6 (FAN2_PWM), R80.1
unnamed: A5.8 (FAN2_TAC), R78.1, R81.1
unnamed: A5.13 (HSIO0_TX+), C109.2
unnamed: A5.15 (HSIO0_TX-), C110.2
unnamed: A5.19 (HSIO1_TX+), C111.2
unnamed: A5.21 (HSIO1_TX-), C112.2
unnamed: A5.25 (HSIO2_TX+), C113.2
unnamed: A5.27 (HSIO2_TX-), C114.2
unnamed: A5.31 (HSIO3_TX+), C115.2
unnamed: A5.33 (HSIO3_TX-), C116.2
unnamed: A5.61 (HSIO6_TX+), C129.2
unnamed: A5.63 (HSIO6_TX-), C130.2
unnamed: A5.37 (HSIO8_TX+), C117.2
unnamed: A5.39 (HSIO8_TX-), C118.2
unnamed: A5.43 (HSIO9_TX+), C119.2
unnamed: A5.45 (HSIO9_TX-), C120.2
unnamed: A5.52 (HSIO10_RX+), C123.2
unnamed: A5.54 (HSIO10_RX-), C124.2
unnamed: A5.49 (HSIO10_TX+), C121.2
unnamed: A5.51 (HSIO10_TX-), C122.2
unnamed: A5.58 (HSIO11_RX+), C127.2
unnamed: A5.60 (HSIO11_RX-), C128.2
unnamed: A5.55 (HSIO11_TX+), C125.2
unnamed: A5.57 (HSIO11_TX-), C126.2
unnamed: A5.5 (SLS_S0), D19.1 (K)
unnamed: A5.155 (SPI_CLK), U5.6 (CLK)
unnamed: A5.161 (SPI_IO2), R88.2, U5.3 (~WP/IO_{2})
unnamed: A5.153 (SPI_IO3), R87.2, U5.7 (~HOLD/~RESET/IO_{3})
unnamed: A5.163 (SPI_MISO/SPI_IO1), U5.2 (DO/IO_{1})
unnamed: A5.159 (SPI_MOSI/SPI_IO0), U5.5 (DI/IO_{0})
unnamed: A5.187 (TCP0_HPD), R89.2
unnamed: A5.185 (TCP1_HPD), R91#2.2
unnamed: A5.115 (VBAT), R82.2
unnamed: A5.133 (~BIOS_SEL), R90#2.1
unnamed: A5.102 (~CLKREQ4), R84.1, R91.1
unnamed: A5.165 (~SPI_CS), U5.1 (~CS)
unnamed: C25.2, R24.1
unnamed: C139.2, R96.1
unnamed: C246.2, TR1.1 (CT), TR1.4 (CT), TR1.7 (CT), TR1.10 (CT)
unnamed: C248.2, TR2.1 (CT), TR2.4 (CT), TR2.7 (CT), TR2.10 (CT)
unnamed: C249.1, R121.2, R122.2, R123.2, R124.2
unnamed: C250.1, R125.2, R126.2, R127.2, R128.2
unnamed: C298.1, TR3.1 (CT), TR3.4 (CT), TR3.7 (CT), TR3.10 (CT)
unnamed: C300.1, TR4.1 (CT), TR4.4 (CT), TR4.7 (CT), TR4.10 (CT)
unnamed: C301.1, R155.2, R156.2, R157.2, R158.2
unnamed: C302.1, R159.2, R160.2, R161.2, R162.2
unnamed: C329.1, TR5.1 (CT), TR5.4 (CT), TR5.7 (CT), TR5.10 (CT)
unnamed: C330.1, R183.2, R184.2, R185.2, R186.2
unnamed: C346.2, C347.2, C349.2, C350.2, C351.2, C352.2, J25.1 (VBUS), J25.7 (VBUS), J25.11 (VBUS), U40.3 (VBUS2), U40.4 (VBUS2), U40.13 (VBUS1), U40.14 (VBUS1)
unnamed: D1.2 (A), M1.3 (Tacho), R1.2, R3.2
unnamed: D2.2 (A), M2.3 (Tacho), R2.2, R4.2
unnamed: D3.2 (A), R9.2
unnamed: D4.2 (A), R12.1
unnamed: D5.2 (A), M3.3 (Tacho), R25.2, R27.2
unnamed: D6.2 (A), M4.3 (Tacho), R26.2, R28.2
unnamed: D7.2 (A), R33.2
unnamed: D8.2 (A), R34.1
unnamed: D9.2 (A), M5.3 (Tacho), R41.2, R43.2
unnamed: D10.2 (A), M6.3 (Tacho), R42.2, R44.2
unnamed: D11.2 (A), R49.2
unnamed: D12.2 (A), R51.1
unnamed: D13.2 (A), M7.3 (Tacho), R58.2, R60.2
unnamed: D14.2 (A), M8.3 (Tacho), R59.2, R61.2
unnamed: D15.2 (A), R66.2
unnamed: D16.2 (A), R68.1
unnamed: D17.2 (A), M9.3 (Tacho), R75.2, R77.2
unnamed: D18.2 (A), M10.3 (Tacho), R76.2, R78.2
unnamed: D19.2 (A), R83.2
unnamed: D20.2 (A), R85.1
unnamed: C132.2, D21.1 (K), L1.1, U6.8 (PH)
unnamed: D22.2 (A), R101.1
unnamed: D22.1 (K), J11.10 (DAS/~DSS/~LED1)
unnamed: D23.2 (A), R102.1
unnamed: D23.1 (K), J12.10 (DAS/~DSS/~LED1)
unnamed: D24.2 (A), R103.1
unnamed: D24.1 (K), J13.10 (DAS/~DSS/~LED1)
unnamed: D25.2 (A), R104.1
unnamed: D25.1 (K), J14.10 (DAS/~DSS/~LED1)
unnamed: D26.2 (A), R105.1
unnamed: D26.1 (K), J15.10 (DAS/~DSS/~LED1)
unnamed: C193.2, C194.2, C195.2, C196.1, C197.2, C198.1, D27.1 (K), J17.1, U7.1 (VDD), U7.9 (VDDA), U7.24 (VDD), U7.48 (VDD)
unnamed: D28.2 (A), R129.1
unnamed: D28.1 (K), U12.30 (LED2)
unnamed: D29.2 (A), R130.1
unnamed: D29.1 (K), U13.30 (LED2)
unnamed: D30.2 (A), R163.1
unnamed: D30.1 (K), U20.30 (LED2)
unnamed: D31.2 (A), R164.1
unnamed: D31.1 (K), U21.30 (LED2)
unnamed: D32.2 (A), R187.1
unnamed: D32.1 (K), U26.30 (LED2)
unnamed: D34.2 (A2), J24.15 (SCL), Q1.3 (D), R202.2
unnamed: D35.2 (A2), J24.16 (SDA), Q2.3 (D), R203.2
unnamed: D36.2 (A2), J24.19 (HPD), R207.2
unnamed: J6.56 (~W_DISABLE1), R97.1
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
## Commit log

2025-08-23 Add programming header and power and reset switches
2025-08-23 Connect PWR_ON and PWR_OK signals
2025-08-24 Add TPS65987D PD controller, switch stm32 to cheaper one
2025-08-24 Connect TPS65987D I2C and Interrupts
2025-08-25 Finish wiring TPS65987D
2025-08-25 Fix TPS65987D Symbol
2025-08-25 Clean up KiCad Backup Files From Git
2025-08-25 Missed a couple backup files
2025-08-25 Fix some diodes and resistors
2025-08-25 Add external BIOS flash
2025-08-25 Switch nics to i226-v
2025-08-26 Remove 0.95V Power Supply, Replace 3.3V Standby Power Supply
2025-08-26 Work though ERC errors
2025-08-26 Re-annotate components
2025-08-26 Add TVS diodes for ESD protection
2025-08-28 Fix esd diodes, add some footprints.
2025-08-28 Add more footprints
2025-08-29 Add USB Type E Header Footprint
2025-08-29 Add footprintss from LCSC
2025-08-30 Lots of tiny capacitors
2025-09-01 Add most passive component footprints
2025-09-02 Add m.2 slot footprints
2025-09-09 Finish fixing footprints
2025-09-10 Begin setting up PCB
2025-09-13 Arranging components
2025-09-13 reposition nix for better space use (maybe)
2025-09-13 Move slots down to make more room for top io
2025-09-14 Fix more footprint issues, continue laying out components
2025-09-14 Place STM32 and fix cpu fan headers
2025-09-14 Place fan headers, adjust other components'
2025-09-21 Lay out Headers
2025-09-26 Start placing capacitors
2025-09-27 Add SFF-8654 Connector
2025-09-28 Start moving components to module sheets to save sheets
2025-09-28 Add RTL8125 to Module Sheet
2025-09-29 Finish RTL8125, Move HDMI
2025-10-25 Add ESD Protection
2025-10-25 Start connecting module
2025-10-26 Finish Connecting Module
2025-10-26 add pretty sections
2025-10-27 Copy modules 2 and 3, remove unnecessary pages
2025-10-27 Add PCIe x1 Slot
2025-11-09 Finish connecting x1 slot. Add pcie clkreq lines
2025-11-09 Re-annotate schematic
2025-11-09 Connect clkreq to nics, fix pcie x1 footprint
2025-11-09 forgot to save schematic
2025-11-24 change sata symbols
2025-11-24 Add 0.95V supply, Fix connectors
2025-11-25 Swap stm32 for extra uart port
2025-11-25 Begin moving IO to module sheets
2025-11-26 Add Ethernet to module sheet
2025-11-28 Switch back to RTL8125B
2025-11-28 Move HDMI to module sheet
2025-12-21 Begin making 2 module card version
2025-12-21 Wire Ethernet switch pcie bus
2026-04-01 Get rid of extra sheets, make module sheets pretty
